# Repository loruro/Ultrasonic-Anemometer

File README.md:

# Ultrasonic Anemometer

<div align="center"></div>

This is Ultrasonic Anemometer project based on AVR ATmega microcontroller.

## Principle of operation

Device measures wind velocity using ultrasounds. Two ultrasonic transducers installed on the end of both pipes send 40 kHz ultrasound signal between each other. Normally the velocity of this signal is the same for both directions. It is equal to the speed of sound, which depends mainly on the air temperature. For dry air and 1000 hPa pressure it can be calculated from:

<div align="center"></div>

where:
* vₚ - speed of sound [m/s]
* θ - air temperature [°C]

At 20 °C it is 343,96 m/s.

If there is a wind, it alters velocity of sound wave propagating in direction parallel to the wind:

<div align="center"></div>

where:
* v₁₂ - velocity of sound wave between point 1 and point 2
* v₂₁ - velocity of sound wave between point 2 and point 1
* vₚ - speed of sound
* vᵥᵥ - speed of wind

Above equations can be transformed into:

<div align="center"></div>

The velocity of sound wave can be acquired by measuring time of flight of this wave between ultrasonic transducers. This is what this device does. First transducer emits ultrasonic impulse and second one receives it. Time between those events is measured and later the situation is reversed. Second transducers emits and first one receives.  
Knowing distance between those transducers, velocity of sound can be finally calculated.

<div align="center"></div>

where:
* d - distance between transducers
* t - time of flight

Velocities in previous equations can be substituted by above time formula:

<div align="center"></div>  

Anemometer has only two ultrasonic transducers. Therefore, it can only measure wind speed in one direction (parallel to line containing both transducers). Measurement in more dimensions can be achievied by adding more transducers.

<div align="center"></div>

Device displays calculated wind speed and its direction on [HD44780 LCD](https://en.wikipedia.org/wiki/Hitachi_HD44780_LCD_controller) display. Under speed value there is a progress bar to next measured value. Unfortunately it takes quite a lot of time to perform all the signal processing calculations on this ATmega (about 46 seconds).  
Red LED is lit while power is supplied to the device. Green LED is blinking while the device is working correctly.  
Red button on the right performs calibration procedure. After pressing button for 2 seconds, [envelope](https://en.wikipedia.org/wiki/Envelope_%28waves%29) will be calculated of the next set of samples acquired by transducers. The result will be stored in EEPROM and used later for signal processing. This has to be done while there is no wind. Along with samples, temperature from DS1820 sensor is also acquired and stored. This calibration data will survive shutdown of the device because of storage in EEPROM.  
On the left side of the device there is a socket for power supply.

<div align="center"> </div>

## Hardware

<div align="center"> </div>

Main part of the device is the AVR [ATmega1284](http://www.atmel.com/devices/atmega1284.aspx) microcontroller. It is slightly overclocked for a better performance. I used 24 MHz quartz crystal (official max. frequency is 20 MHz). Controller is programmed with ISP interface. I used simple and cheap [USBasp](http://www.fischl.de/usbasp/) programmer for it.  
Calibration button was connected together with resistor, capacitor and diode which do hardware [debouncing](https://en.wikipedia.org/wiki/Switch#Contact_bounce).  
All of the electronics are powered by 5 V supplied by onboard 7805 voltage regulator. It takes voltage straight from power socket. I used external 9 V power supply, but slightly higher voltage would be OK too (not too much to not overheat 7805 regulator). Along with it there is simple protection overcurrent and inverted voltage. Also there is ICL7660 -5 V voltage generator. It's used for powering multiplexer and operational amplifiers.  
HD44780 display is connected in 4-bit mode and busy bit reading.  
DS1820 temperature sensor uses 1-Wire interface, but has option for powering it via additional VDD pin. I used this option for better stability.  
Analog part of the device needs more explanation. Some of the signals here were measured by an oscilloscope. Microcontroller sends square wave through GENERATOR_OUT line to ultrasonic transducers.

<div align="center"></div>

Multiplexer 74HC4052 directs it to either left or right transducer. Multiplexer is controlled by SWITCH_CHANNEL from ATmega. Transducers used in project are narrowband and designed for 40 kHz signal. Experimentally I found out that 40268 Hz signal gives the best amplitude. Transducers are connected with board by shielded cable. While signal from microcontroller is directed to one of them, signal from the other one is directed by multiplexer to amplifiers. Here is the signal before them:

<div align="center"></div>

First is an [inverting amplifier](https://en.wikipedia.org/wiki/Operational_amplifier_applications#Inverting_amplifier):

<div align="center"></div>

Amplified signal:

<div align="center"></div>

Later signal goes to [summing amplifier](https://en.wikipedia.org/wiki/Operational_amplifier_applications#Summing_amplifier), which again amplifies and adds offset to it. Entire signal has to be voltage positive because ADC used in the device cannot work with negative voltage.

<div align="center"></div>

Amplified signal:

<div align="center"></div>

For final step I used [integrator](https://en.wikipedia.org/wiki/Operational_amplifier_applications#Inverting_integrator), which acts as low-pass filter. Any frequencies which are higher than our ultrasonic signal should be filtered out. Transfer function of the filter:

<div align="center"></div>

And its Bode plot:

<div align="center"></div>

Signal after filtering:

<div align="center"></div>

After all the operational amplifiers, signal finally goes to ADS7822P analog-to-digital converter. It sends converted digital signal to microcontroller through SPI interface. ATmega here is a master. This ADC has a resolution of 12 bits and max. frequency of 200 kHz. Because of clock dividers in ATmega and clock cycles needed to handle SPI, I managed to get sampling frequency of 157.9 kHz. [Nyquist–Shannon–Kotelnikov sampling theorem](https://en.wikipedia.org/wiki/Nyquist%E2%80%93Shannon_sampling_theorem) states that the sampling frequency should be at least 80536 Hz, so it is fulfilled. Analog signal has maximum value of about 4 V, so to increase voltage resolution I attached voltage divider to VREF pin of ADC, which gives voltage of about 4.359 V. This results in voltage resolution of 1.064 mV.  
Analog part of the device uses different ground than the rest of the device. It reduces noise derived from high frequency digital signals. Digital ground and analog ground are connected together at one point, close to the power supply.

Electrical schematic and PCB layout were designed using [EAGLE](https://cadsoft.io/) application. Tracks on PCB were designed using EAGLE Autorouter. That's why it's so ugly :)  
Photos of interior:

<div align="center">  </div>

## Signal processing

After acquiring by microcontroller, digital samples look like this:

<div align="center"></div>

Those samples should be analyzed without offset, so average value is calculated and subtracted from them:

<div align="center"></div>

For getting precise time of flight of ultrasonic impulse I decided to calculate envelope of the acquired signal and [cross correlate](https://en.wikipedia.org/wiki/Cross-correlation) it with the calibration signal stored in EEPROM. To get envelope of signal, a magnitude of its [analytic representation](https://en.wikipedia.org/wiki/Analytic_signal) can be calculated. To get analytic signal, [Hilbert transform](https://en.wikipedia.org/wiki/Hilbert_transform) has to be calculated first. I used the following discrete formula to acquire it:

<div align="center"></div>

where:

<div align="left"></div>

and
* x - original signal
* N - number of samples

Analytic signal can now be calculated with the following formula:

<div align="center"></div>

Result:

<div align="center"></div>

Now the envelope can be cross correlated with the envelope of calibration signal. I used following formula for discrete cross correlation:

<div align="center"></div>

Distance between the maximal value and Y axis should determine time of flight of ultrasonic signal:

<div align="center"></div>

I also tried calculating only the cross correlation of present and calibration signals, but results were far from being correct. I also tried calculating cross correlation first and then the envelope of it. Results were almost as good as the currently used method, but still they were worse.

I observed that the top part of the calculated cross correlation looks similar to quadratic function. To increase resolution and extract more information from it I decided to use quadratic regression. 31 highest samples are used to approximate quadratic function using following formulas:

<div align="center"></div>

where:
* x - function arguments
* y - function value
* ( ¯ ) - average value

Coefficients can now be calculated (coefficient C is not needed):

<div align="center"></div>

And finally maximum of the function can be calculated:

<div align="center"></div>

This maximum is used to calculate the time of flight. Here is comparison of signal and approximated quadratic function:

<div align="center"></div>

Distance between the maximal value and Y axis multiplied by 6333 ns results only in signal time of flight difference between conditions with wind and without wind. To get total time of fligh there has to be added time of flight during windless conditions. This time is calculated using temperature acquired during calibration by using formula from the beggining of the article. Distance between transducers also has to be known. It's 27 cm. Any later temperature changes should not affect the final result.  
Knowing the total signal time of flight, final wind speed value is calculated.

## Software

Software for the ATmega1284 microcontroller was developed using Atmel Studio IDE with AVR8 GNU Toolchain. It contains avr-libc libraries and avr-gcc compiler. Optimization flag **_-Os_** was set for compilation. All used flags are below:
```shell
avr-gcc -x c -funsigned-char -funsigned-bitfields -DNDEBUG -DF_CPU=24000000UL -Os -ffunction-sections -fdata-sections -fpack-struct -fshort-enums -mrelax -Wall -mmcu=atmega1284 -c -std=gnu99 -MD -MP -MF "$(@:%.o=%.d)" -MT"$(@:%.o=%.d)" -MT"$(@:%.o=%.o)"
```
Fuse bits are configured as follows:

| Fuse Low | Fuse High | Extended Fuse |
| :------: |:---------:| :-----------: |
|   0xF7   |   0xD1    |     0xFC      |

Pretty online fuse calculator showing this configuration is [here](http://eleccelerator.com/fusecalc/fusecalc.php?chip=atmega1284p&LOW=F7&HIGH=D1&EXTENDED=FC&LOCKBIT=FF). Fuse Low is configured to allow clock source from 24 MHz quartz crystal. Fuse High, among other things, disables JTAG interface, so more pins can be used as GPIO. Extended Fuse enables Brown-out detection at level 4.3 V.

One of the most important fragment of code is shown below:
```c
inline void getDataFromAdc(uint16_t *data) {
  // Activating ADC.
  SPI_SS_LOW;
  // Starting transmission.
  SPDR = 0x00;

  // Waiting for end of transmission.
  // NOP causes loop to check end of transmission flag at the most optimal time.
  asm volatile("nop"::);
  while(!(SPSR & _BV(SPIF)));

  // Starting another transmission.
  SPDR = 0x00;
  // Saving byte from previous transmission.
  *((uint8_t*)data + 1) = SPDR;

  // Waiting for end of transmission. This time three NOP's were needed.
  asm volatile(
    "nop\n\t"
    "nop\n\t"
    "nop\n\t"::
  );
  while(!(SPSR & _BV(SPIF)));

  // Saving byte from transmission.
  *((uint8_t*)data + 0) = SPDR;
  // Deactivating ADC.
  SPI_SS_HIGH;
}
```
This function is responsible for acquiring samples from ADC. Execution time of it is significant, because sampling frequency depends on it. <i>SPI_SS_LOW</i> macro drives SS line low on SPI interface. It enables ADC. Afterwards, writing 0 to SPDR register begins transmission. Microcontroller is transmitting this 0 over MOSI line (which is not even connected to ADC), but at the same time, it receives data byte over MISO line. <i>while(!(SPSR & _BV(SPIF)))</i> waits for the end of transmission. Because checking for SPIF flag in loop takes a few clock cycles, adding <i>asm volatile("nop"::)</i> ensures that the flag is checked right after end of transmission. This solution was found by analyzing assembly code during simulator debugging. Right after that, another transmission starts. Afterwards, previous byte is saved in variable. SPDR register for transmitted byte is different than SPDR for received byte, so this sequence was used just to save some clock cycles. SPIF is checked again for end of transmission, but now three NOPs were needed. Later, new byte is saved in variable and <i>SPI_SS_HIGH</i> drives SS line high and disables ADC. Restarting ADC is needed between every sample.

Generated assembly from above code is shown below:
```nasm
cbi    0x05, 4
out    0x2e, r1
nop
in     r0, 0x2d
sbrs   r0, 7
rjmp   .-6
out    0x2e, r1
in     r18, 0x2e
movw   r30, r24
subi   r30, 0xA7
sbci   r31, 0xFE
std    Z+1, r18
nop
nop
nop
in     r0, 0x2d
sbrs   r0, 7
rjmp   .-6
in     r18, 0x2e
st     Z, r18
sbi    0x05, 4
adiw   r24, 0x02
cpi    r24, 0xC0
ldi    r18, 0x03
cpc    r25, r18
brne   .-52
```
Execution of this code takes exactly 152 clock cycles. For 24 MHz clock, it gives 6333 ns. It is equivalent to sampling frequency of 157.9 MHz.

In this program there are no floating point numbers, because ATmega microcontrollers don't have hardware support for them, which would result in very long computation time and large memory consumption. Trigonometric functions needed for calculations were implemented as lookup tables.

## Conclusion

I tested the device with typical household fan. Result of the measurements seem to be OK. Unfortunately I don't have access to any professional hardware, which would verify it.  
46 seconds needed for calculating wind speed is a bit too long time. More powerful microcontroller should have been used or a different signal processing method. ATmega microcontrollers are very slow comparing to modern ones.  
Despite it, while creating this device I learned many new things about electronics, digital signal processing and programming embedded systems in C. Also I Learned how does ultrasonic anemometer works.

<br /><span xmlns:dct="http://purl.org/dc/terms/" property="dct:title">Ultrasonic Anemometer</span> by <span xmlns:cc="http://creativecommons.org/ns#" property="cc:attributionName">Karol Leszczyński</span> is licensed under a <a rel="license" href="http://creativecommons.org/licenses/by-sa/4.0/">Creative Commons Attribution-ShareAlike 4.0 International License</a>.

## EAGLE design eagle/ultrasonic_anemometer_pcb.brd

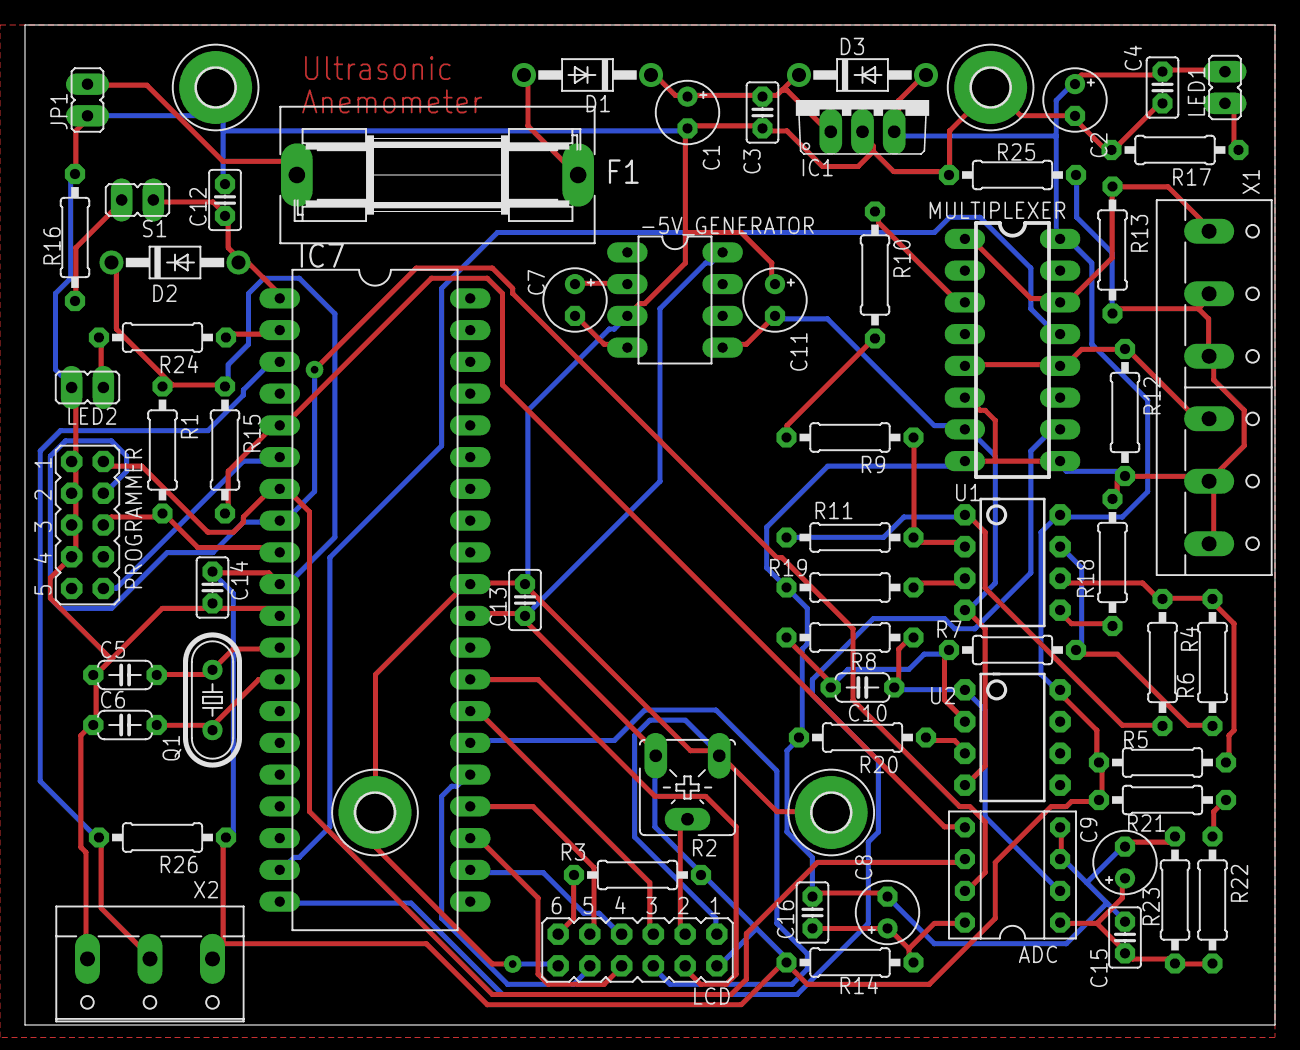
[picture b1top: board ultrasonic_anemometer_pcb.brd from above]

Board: 2 copper layers, 100.0 x 80.0 mm, 66 parts (0 on the bottom side), 49 nets.

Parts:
-5V_GENERATOR: ICL7660; DIL08
ADC: ADS7822P; DIL08
C1, C2: 100μF; E2,5-5
C3, C4, C12, C13, C14, C15, C16: 100nF; C025-025X050
C5, C6: 22pF; C050-024X044
C7, C8, C9, C11: 10μF; E2,5-5
C10: 18pF; C050-024X044
D1, D2, D3: 1N4004; DO41-10
F1: SH22,5A
H1, H2, H3, H4: MOUNT-PAD-ROUND3.0; 3,0-PAD
IC1: 7805; TO220V
IC7: ATMEGA1284; DIL40
JP1: JP1
LCD: JP6Q
LED1, LED2: JP1
MULTIPLEXER: 74HC4052; DIL16
PROGRAMMER: JP5Q
Q1: 25Mhz; HC49/S
R1, R4, R7, R8, R10, R12, R13, R15, R19, R23: 10kΩ; 0207/10
R2: 100kΩ; CA6V
R3: 220Ω; 0207/10
R5: 220kΩ; 0207/10
R6: 100kΩ; 0207/10
R9, R20, R26: 4.7kΩ; 0207/10
R11: 47kΩ; 0207/10
R14: 4.7Ω; 0207/10
R16: 330Ω; 0207/10
R17, R22, R24: 1kΩ; 0207/10
R18: 8.2kΩ; 0207/10
R21: 470Ω; 0207/10
R25: 0Ω; 0207/10
S1: JP1
U1, U2: OPAMP-DUALDIP; DIP08
X1: W237-6
X2: W237-103

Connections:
-5V: -5V_GENERATOR.5, C11.-, MULTIPLEXER.7, U1.4, U2.4
AGND: ADC.3, ADC.4, C8.-, C9.-, C15.1, C16.2, MULTIPLEXER.6, MULTIPLEXER.8, MULTIPLEXER.9, R12.2, R13.2, R18.2, R19.2, R20.2, R23.2, R25.1, X1.2, X1.3, X1.5, X1.6
DS1820_SENSOR: IC7.3, R26.2, X2.2
GENERATOR_OUT: IC7.19, MULTIPLEXER.13
GND: -5V_GENERATOR.3, C1.-, C2.-, C3.2, C4.2, C5.1, C6.1, C11.+, C12.2, C13.2, C14.2, H1.B3,0, H2.B3,0, H3.B3,0, H4.B3,0, IC1.2, IC7.11, IC7.31, JP1.1, LCD.1, LCD.12, LED2.2, PROGRAMMER.1, PROGRAMMER.3, PROGRAMMER.5, PROGRAMMER.7, R2.A, R16.1, R17.2, R25.2, X2.3
LCD_D4: IC7.22, LCD.7
LCD_D5: IC7.23, LCD.8
LCD_D6: IC7.24, LCD.9
LCD_D7: IC7.25, LCD.10
LCD_E: IC7.26, LCD.6
LCD_RS: IC7.28, LCD.4
LCD_RW: IC7.27, LCD.5
MISO: ADC.6, IC7.7, PROGRAMMER.2
MOSI: IC7.6, PROGRAMMER.10
unnamed: F1.1, JP1.2
unnamed: D1.A, F1.2
unnamed: C1.+, C3.1, D1.C, D3.C, IC1.1
unnamed: MULTIPLEXER.1, MULTIPLEXER.14, R13.1, X1.1
unnamed: MULTIPLEXER.5, MULTIPLEXER.12, R12.1, X1.4
unnamed: R9.1, R11.2, U1.2
unnamed: R19.1, U1.3
unnamed: R18.1, U1.5
unnamed: R20.1, U2.3
unnamed: C12.1, D2.A, IC7.1, S1.1
unnamed: C5.2, IC7.12, Q1.2
unnamed: C6.2, IC7.13, Q1.1
unnamed: C10.2, R7.1, R8.2, U2.2
unnamed: -5V_GENERATOR.2, C7.+
unnamed: -5V_GENERATOR.4, C7.-
unnamed: R9.2, R10.2
unnamed: R4.1, R5.1, R6.2, U1.6
unnamed: R6.1, R7.2, U1.7
unnamed: LCD.11, R3.2
unnamed: R16.2, S1.2
unnamed: LCD.3, R2.S
unnamed: ADC.1, C9.+, C15.2, R22.2, R23.1
unnamed: LED2.1, R24.2
unnamed: LED1.1, R17.1
unnamed: ADC.8, C8.+, C16.1, R14.2
unnamed: R21.2, R22.1
unnamed: ADC.2, C10.1, R8.1, U2.1
unnamed: IC7.2, R24.1
unnamed: R4.2, R11.1, U1.1
unnamed: MULTIPLEXER.3, R10.1
RESET: IC7.9, PROGRAMMER.6, R1.2
SCK: ADC.7, IC7.8, PROGRAMMER.4
SS: ADC.5, IC7.5, R15.2
SWITCH_CHANNEL: IC7.20, MULTIPLEXER.10
VCC: -5V_GENERATOR.8, C2.+, C4.1, C13.1, C14.1, D2.C, D3.A, IC1.3, IC7.10, IC7.30, LCD.2, LED1.2, MULTIPLEXER.16, R1.1, R2.E, R3.1, R5.2, R14.1, R15.1, R21.1, R26.1, U1.8, U2.8, X2.1

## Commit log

2016-03-03 Added sample images.
2016-03-03 Updated README.
2016-11-01 Added source code.
2016-11-02 Added Eagle schematic files.
2016-11-02 Small fixes on Eagle pcb schematic.
2016-11-02 Added images of schematic and pcb.
2016-11-02 Moved software license file and added hardware license.
2016-11-04 Removed some old images and added new ones.
2016-11-05 Added more images.
2016-11-10 Small fix in ADC driver.
2016-12-14 Create gh-pages branch via GitHub
2021-05-15 Set theme jekyll-theme-architect and migrate Page Generator content

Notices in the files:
parts and their libraries:
SparkFun-AnalogIC: Licensing:Creative Commons ShareAlike 4.0 International - https://creativecommons.org/licenses/by-sa/4.0
